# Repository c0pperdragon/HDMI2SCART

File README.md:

# HDMI2SCART
An adapter to drive a 15kHz analog monitor from a HDMI video source.
Its main purpose is to allow authentic look and feel for an emulator based
retro gaming solution. 
A second purpose is to interface with an RGBtoHDMI device for Lumacode decoding.

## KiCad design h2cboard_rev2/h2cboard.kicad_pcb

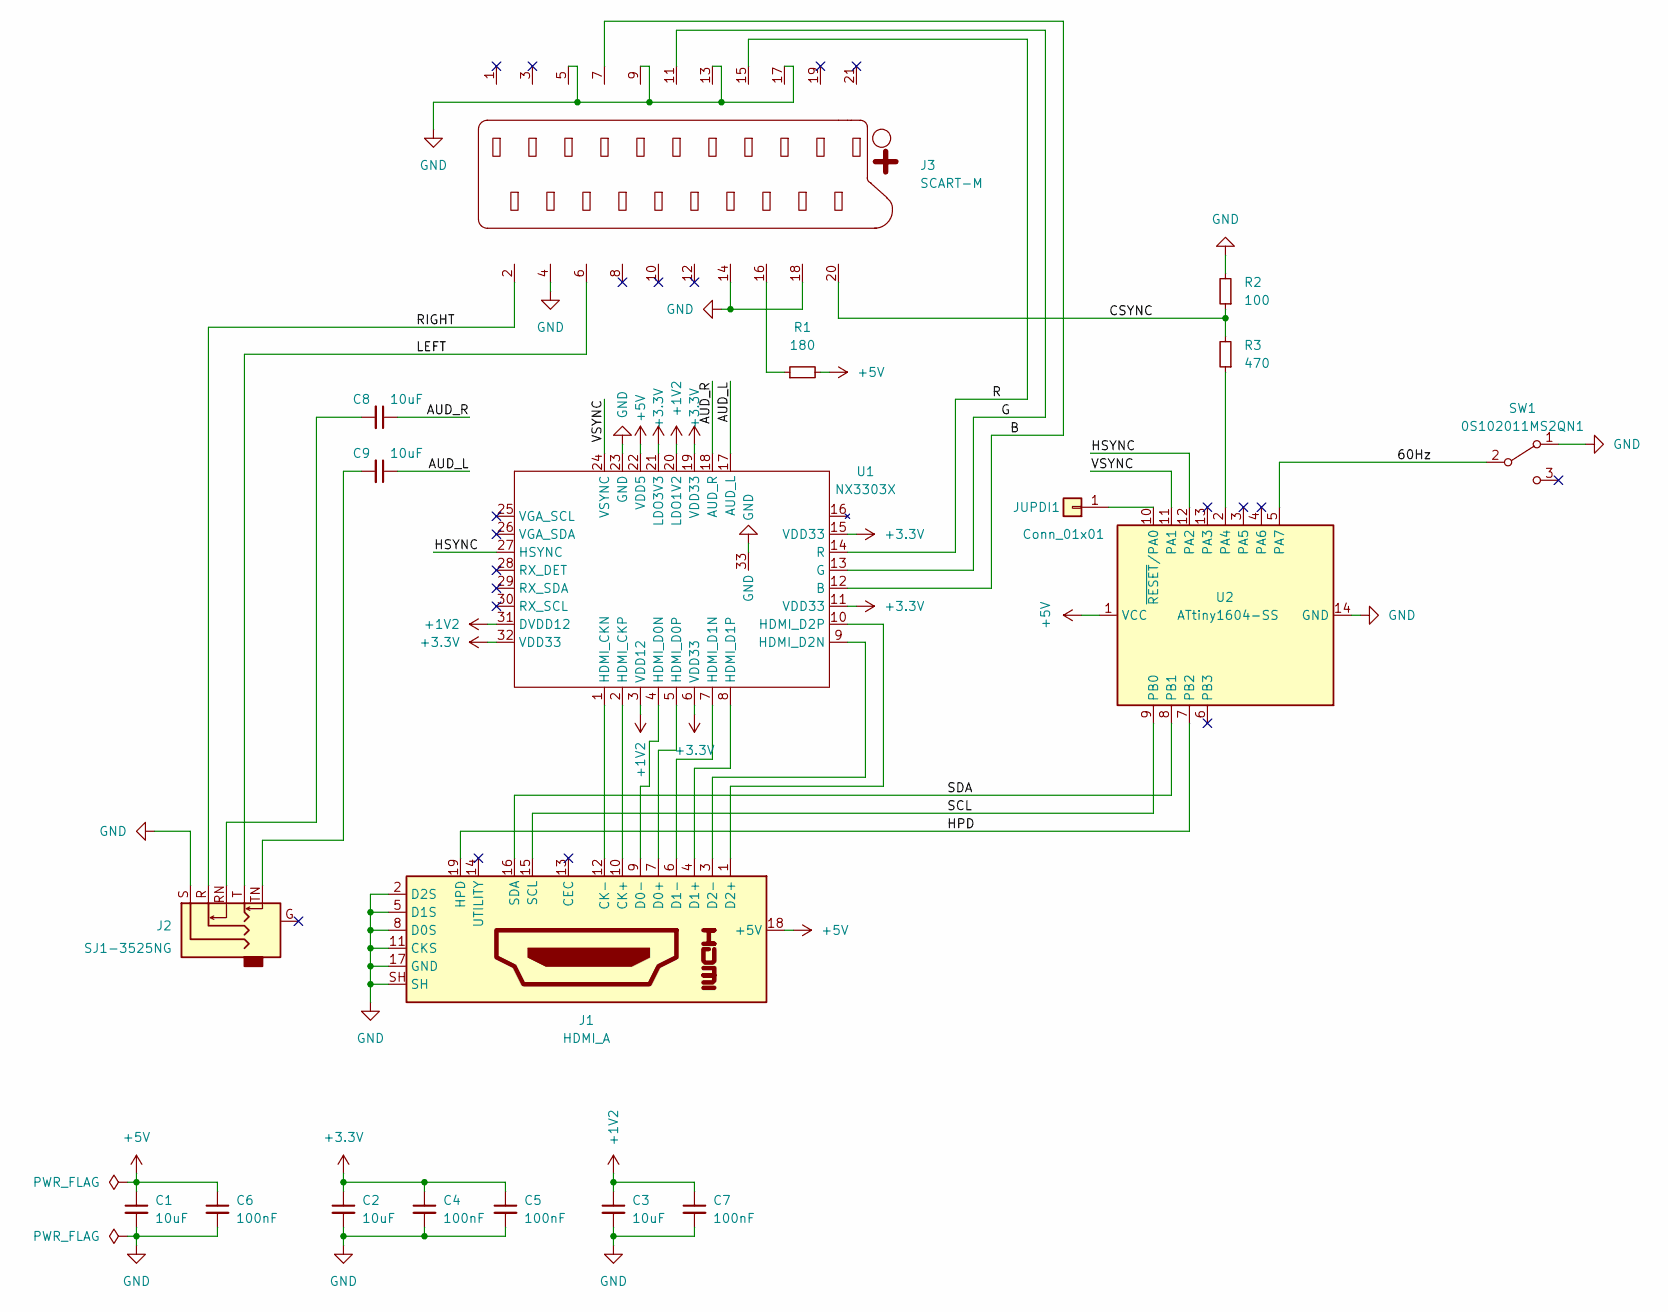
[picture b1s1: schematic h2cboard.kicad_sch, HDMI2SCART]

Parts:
C1, C2, C3, C8, C9: 10uF; C_0805_2012Metric
C4, C5, C6, C7: 100nF; C_0603_1608Metric
J1: HDMI_A; FCI_10029449-11-5B13-5DRLF
J2: SJ1-3525NG; audio_jack
J3: SCART-M; SCART_Edge_mount
JUPDI1: Conn_01x01; PinHeader_1x01_P2.54mm_Vertical
R1: 180; R_0805_2012Metric
R2: 100; R_0805_2012Metric
R3: 470; R_0805_2012Metric
SW1: 0S102011MS2QN1; SW_Slide_1P2T_CK_OS102011MS2Q
U1: NX3303X; QFN-32-1EP_5x5mm_P0.5mm_EP3.1x3.1mm_ThermalVias
U2: ATtiny1604-SS; SOIC-14_3.9x8.7mm_P1.27mm

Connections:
+1V2: C3.1, C7.1, U1.3 (VDD12), U1.20 (LDO1V2), U1.31 (DVDD12)
+3.3V: C2.1, C4.1, C5.1, U1.6 (VDD33), U1.11 (VDD33), U1.15 (VDD33), U1.19 (VDD33), U1.21 (LDO3V3), U1.32 (VDD33)
+5V: C1.1, C6.1, J1.18 (+5V), R1.2, U1.22 (VDD5), U2.1 (VCC)
/60Hz: SW1.2 (B), U2.5 (PA7)
/AUD_L: C9.1, U1.17 (AUD_L)
/AUD_R: C8.1, U1.18 (AUD_R)
/B: J3.7, U1.12 (B)
/CSYNC: J3.20, R2.1, R3.2
/G: J3.11, U1.13 (G)
/HPD: J1.19 (HPD), U2.7 (PB2)
/HSYNC: U1.27 (HSYNC), U2.12 (PA2)
/LEFT: J2.T, J3.6
/R: J3.15, U1.14 (R)
/RIGHT: J2.R, J3.2
/SCL: J1.15 (SCL), U2.9 (PB0)
/SDA: J1.16 (SDA), U2.8 (PB1)
/VSYNC: U1.24 (VSYNC), U2.11 (PA1)
GND: C1.2, C2.2, C3.2, C4.2, C5.2, C6.2, C7.2, J1.2 (D2S), J1.5 (D1S), J1.8 (D0S), J1.11 (CKS), J1.17 (GND), J1.SH, J2.S, J3.4, J3.5, J3.9, J3.13, J3.14, J3.17, J3.18, R2.2, SW1.1 (A), U1.23 (GND), U1.33 (GND), U2.14 (GND)
unnamed: C8.2, J2.RN
unnamed: C9.2, J2.TN
unnamed: J1.10 (CK+), U1.2 (HDMI_CKP)
unnamed: J1.12 (CK-), U1.1 (HDMI_CKN)
unnamed: J1.7 (D0+), U1.5 (HDMI_D0P)
unnamed: J1.9 (D0-), U1.4 (HDMI_D0N)
unnamed: J1.4 (D1+), U1.8 (HDMI_D1P)
unnamed: J1.6 (D1-), U1.7 (HDMI_D1N)
unnamed: J1.1 (D2+), U1.10 (HDMI_D2P)
unnamed: J1.3 (D2-), U1.9 (HDMI_D2N)
unnamed: J3.16, R1.1
unnamed: JUPDI1.1, U2.10 (~RESET/PA0)
unnamed: R3.1, U2.2 (PA4)

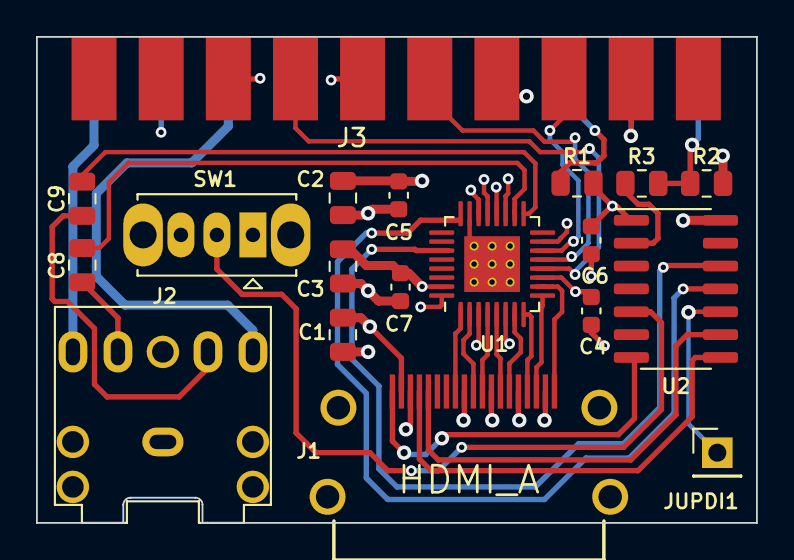
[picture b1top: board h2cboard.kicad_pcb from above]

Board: 4 copper layers, 40.0 x 27.0 mm, 19 parts (1 on the bottom side), 31 nets.

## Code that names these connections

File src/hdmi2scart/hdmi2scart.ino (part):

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void setup() 
{
  CLKCTRL.MCLKCTRLB = B00000000; // use full system clock for peripherials
  pinMode(8, INPUT);        // pin 11/PA1 (VSYNC)
  pinMode(9, INPUT);        // pin 12/PA2 (HSYNC)
  pinMode(0, OUTPUT);       // pin 2/PA4 (CSYNC)
  digitalWrite(0,HIGH);

  pinMode(7, INPUT_PULLUP); // pin 9/PB0 (SCL)
  pinMode(6, INPUT_PULLUP); // pin 8/PB1 (SDA)

  pinMode(3, INPUT_PULLUP); // pin 5/PA7 (60Hz selector)
  pinMode(5, OUTPUT);       // pin 7/PB2 (hot-plug detection)
  digitalWrite(5,HIGH);
  
  startcsync();
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// set up programmable logic to synthesize csync from VSYNC and HSYNC (negative polarity by default)
void startcsync()
{
  // configure LUT1 to invert incomming HSYNC from PA2 and provide signal on async channel 1
  EVSYS.ASYNCCH0 = 0x0C;        // async channel 0 use data from PA2
  EVSYS.ASYNCUSER3 = 0x3;       // EV0 input for LUT1 is taken from async channel 0
  CCL.LUT1CTRLB   = 0x03;       // input 1 unused, input 0 from EV0 input  
  CCL.LUT1CTRLC   = 0x00;       // input 2 unused
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  TCB0.CCMP = 1100;         // nominally 55us duration of single-shot pulse 
  // finally combine signals in asynchronous LUT to use the one-shot pulse during vsync, otherwise the hsync
  EVSYS.ASYNCUSER2 = 0x04;      // EV0 input for LUT0 is taken from async channel 1
  CCL.LUT0CTRLB   = 0x57;       // input 1 from PA1, input 0 from TCB state
  CCL.LUT0CTRLC   = 0x03;       // input 2 from EV0 input which is async channel 1 (from LUT1)
  CCL.TRUTH0      = B00001101;  // truth table for using negative vsync input
  CCL.LUT0CTRLA   = B00001001;  // enable LUT0 and dedicated output pin
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
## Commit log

2024-02-05 Make 1440x288 EDID compatible with RGBtoHDMI and Windows
2024-02-07 Implement EDID sending with native register access
2024-02-08 Create CSYNC in a more standard conform manner
2024-02-09 Improve CSYNC generation
2024-02-16 Ongoing experiments
2024-02-18 PCB design done
2024-02-19 Firmware for the finished part
2024-02-19 Make gerbers
2024-02-23 Test more adapters
2024-03-08 More details on compatible ICs
2024-03-09 Finish firmware
2024-03-17 Product pictures
2024-12-25 note used vga adapter
2025-02-23 Second revision for different IC
2025-02-24 New PCB layout for rev.2
2026-05-18 Update DAC overview table. Add comment about noise-supression botch.
2026-05-30 Noise suppression filter of 10nF is already good enough, and should not filter too much high frequencies out of the audio.
